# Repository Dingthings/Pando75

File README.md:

# Pando75
 Revised 75% keyboard based on Numpad65 project, inclusion of OLED and encoder module

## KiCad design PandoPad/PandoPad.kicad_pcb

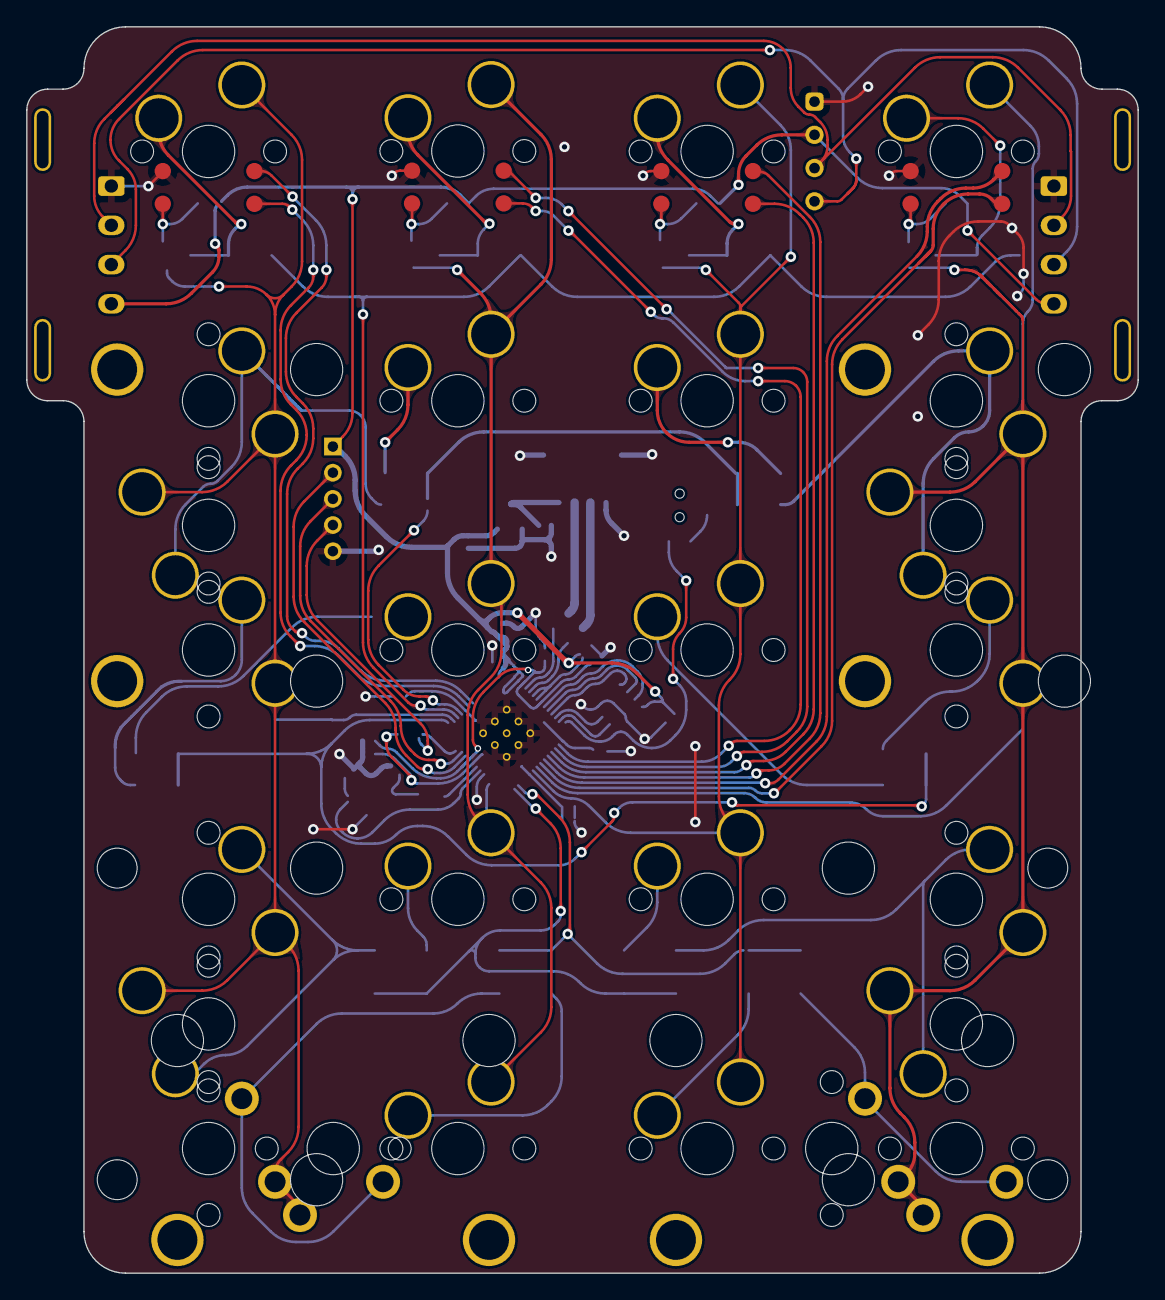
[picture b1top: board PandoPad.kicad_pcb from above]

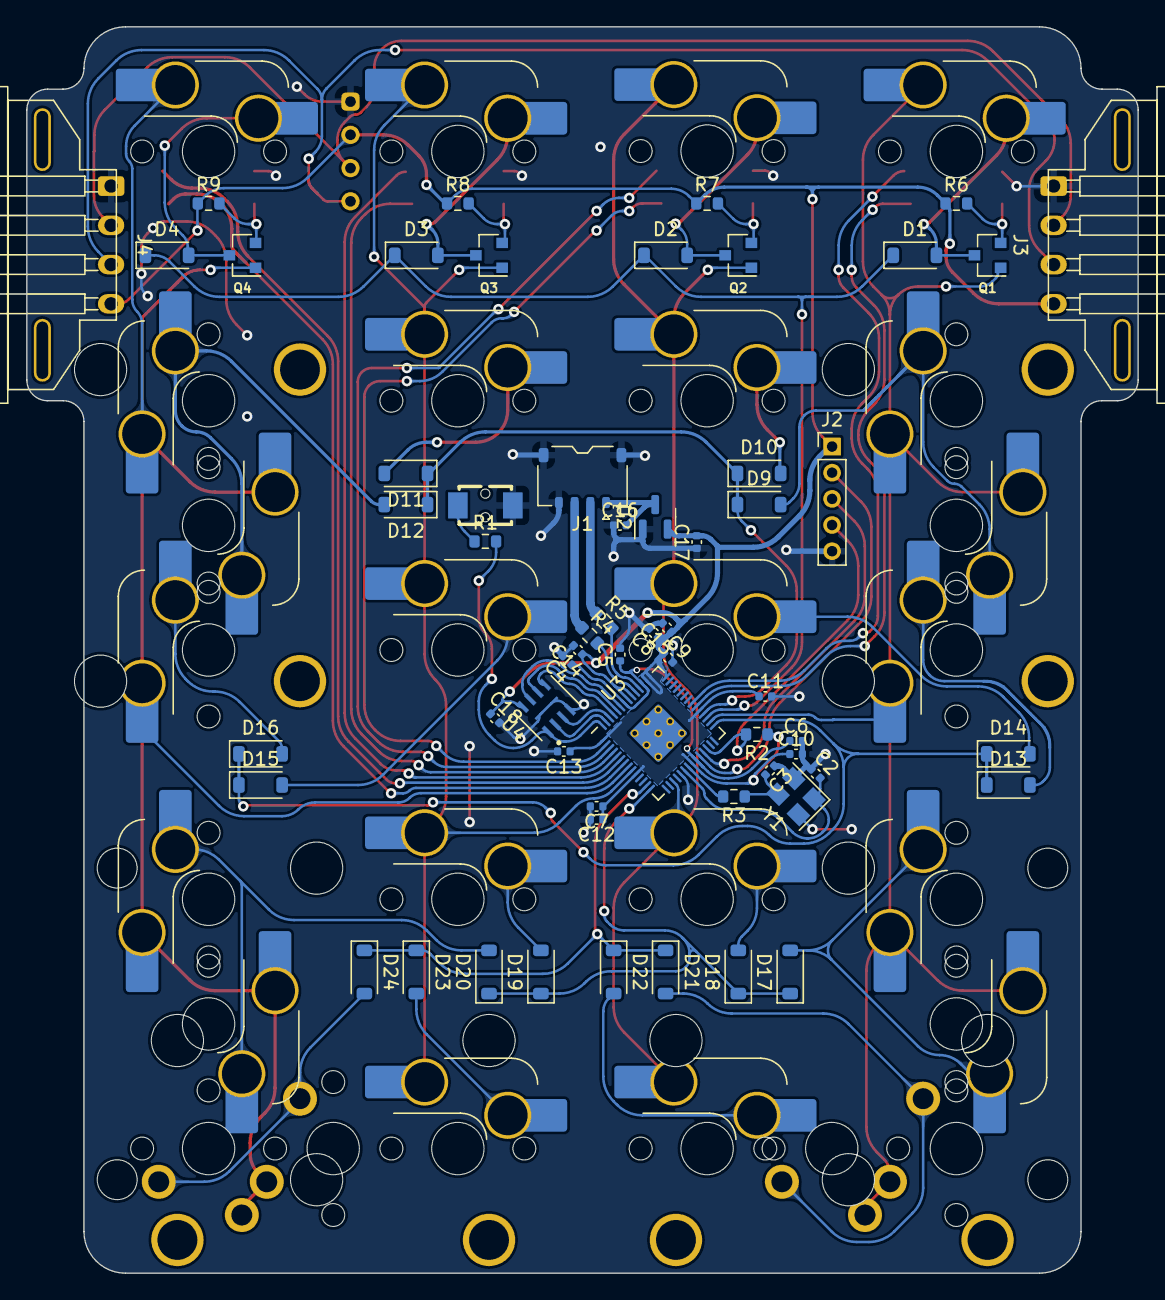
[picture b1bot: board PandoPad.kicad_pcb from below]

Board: 2 copper layers, 84.9 x 95.2 mm, 92 parts (57 on the bottom side), 64 nets.

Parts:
C2, C3: 22pF; C_0402_1005Metric
C4, C8, C16, C17: 1uF; C_0402_1005Metric
C5, C6, C9, C10, C11, C12, C13, C14, C15, C18: 100nF; C_0402_1005Metric
C7: 10uF; C_0402_1005Metric
D1, D2, D3, D4, D9, D10, D11, D12, D13, D14, D15, D16, D17, D18, D19, D20, D21, D22, D23, D24: 1N4148W; D_SOD-123
J1: 78171-0004; JST_ACH_BM04B-ACHSS-A-GAN-ETF_1x04-1MP_P1.20mm_Vertical
J2: Conn_01x05; PinHeader_1x05_P2.00mm_Vertical
J3: MalePogo; 1x04_3.00mm_Magnetic Pogo_Male
J4: FemalePogo; 1x04_3.00mm_Magnetic Pogo_Female
K1, K2, K3, K4: SW_Hotswap_Kailh_MX_plated_1.00u_Enc_Standalone
K9: 7; SW_Hotswap_Kailh_MX_plated_1.00u_Vias
K10: 8; SW_Hotswap_Kailh_MX_plated_1.00u_Vias
K11: 9; SW_Hotswap_Kailh_MX_plated_1.00u_Vias
K12: Right+; SW_Hotswap_Kailh_MX_plated_1.00u_Vias
K13: 4; SW_Hotswap_Kailh_MX_plated_1.00u_Vias
K14: 5; SW_Hotswap_Kailh_MX_plated_1.00u_Vias
K15: 6; SW_Hotswap_Kailh_MX_plated_1.00u_Vias
K16: OPT2; SW_Hotswap_Kailh_MX_plated_1.00u_Vias
K17: 1; SW_Hotswap_Kailh_MX_plated_1.00u_Vias
K18: 2; SW_Hotswap_Kailh_MX_plated_1.00u_Vias
K19: 3; SW_Hotswap_Kailh_MX_plated_1.00u_Vias
K20: REnt; SW_Hotswap_Kailh_MX_plated_1.00u_Vias
K22: LZero; SW_Hotswap_Millmax_1.00u
K23, K24: .; SW_Hotswap_Kailh_MX_plated_1.00u_Vias
K25: OPT5; SW_Hotswap_Millmax_1.00u
KO-1: Left+; SW_Hotswap_Kailh_MX_plated_1.00u_Vias
KO-2: OPT1; SW_Hotswap_Kailh_MX_plated_1.00u_Vias
KO-3: LEnt; SW_Hotswap_Kailh_MX_plated_1.00u_Vias
KO-4: OPT3; SW_Hotswap_Kailh_MX_plated_1.00u_Vias
KO-5: OPT4; SW_Hotswap_Millmax_1.00u
KO-6: OPT6; SW_Hotswap_Millmax_1.00u
P1: OLED2; OLED_v2
Q1, Q2, Q3, Q4: PMOS; SOT-23
R1, R3, R6, R7, R8, R9: 1k; R_0603_1608Metric
R2: R_Small; R_0603_1608Metric
R4, R5: 22R; R_0603_1608Metric
S1: PlusR; STAB_MX_P_2u
S2: EnterR; STAB_MX_2u
S3: PlusL; STAB_MX_P_2u
S4: EnterL; STAB_MX_2u
S5: ZeroR; STAB_MX_P_2u
S6: ZeroL; STAB_MX_P_2u
SW5: SW_Push; SW_C843666
U2: XC6206PxxxMR-Regulator_Linear; SOT-23
U3: RP2040; RP2040-QFN-56
U4: W25Q32JVUUIQ; SON80P400X300X60-10N
Y1: 12MHz; Crystal_SMD_3225-4Pin_3.2x2.5mm

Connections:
+1V1: C4.1, C5.1, C6.1, U3.23 (DVDD), U3.45 (VREG_VOUT), U3.50 (DVDD)
+3V3: C7.1, C8.1, C9.1, C10.1, C11.1, C12.1, C13.1, C14.1, C15.1, C17.2, C18.1, J2.1, J3.1, J4.1, P1.3, R2.1, R6.1, R7.1, R8.1, R9.1, U2.2 (VO), U3.1 (IOVDD), U3.10 (IOVDD), U3.22 (IOVDD), U3.33 (IOVDD), U3.42 (IOVDD), U3.43 (ADC_AVDD), U3.44 (VREG_VIN), U3.48 (USB_VDD), U3.49 (IOVDD), U4.8 (VCC)
+5V: C16.2, J1.1, U2.3 (VI)
/D_+: R4.2, U3.47 (D+)
/D_-: R5.2, U3.46 (D-)
/XTAL_O: C3.2, R3.1, Y1.3
/~USB_BOOT: R1.1, SW5.2
CS: R1.2, U3.56 (QSPI_SS_N), U4.1 (~CS)
D_N: J1.2, R5.1
D_P: J1.3, R4.1
E1A: K1.A, U3.34 (GPIO22)
E1B: K1.B, U3.35 (GPIO23)
E2A: K2.A, U3.2 (GPIO0)
E2B: K2.B, U3.3 (GPIO1)
E3A: K3.A, U3.4 (GPIO2)
E3B: K3.B, U3.5 (GPIO3)
E4A: K4.A, U3.7 (GPIO5)
E4B: K4.B, U3.6 (GPIO4)
GND: C2.1, C3.1, C4.2, C5.2, C6.2, C7.2, C8.2, C9.2, C10.2, C11.2, C12.2, C13.2, C14.2, C15.2, C16.1, C17.1, C18.2, J1.4, J1.MP (MountPin), J2.5, J3.4, J4.4, K1.C, K2.C, K3.C, K4.C, P1.4, SW5.1, U2.1 (GND), U3.19 (TESTEN), U3.57 (GND), U4.4 (GND), U4.9 (EXP), U4.10 (EXP), Y1.2, Y1.4
unnamed: D1.2 (A), K1.2, Q1.3 (S)
unnamed: D2.2 (A), K2.2, Q2.3 (S)
unnamed: D3.2 (A), K3.2, Q3.3 (S)
unnamed: D4.2 (A), K4.2, Q4.3 (S)
unnamed: D9.2 (A), K9.1, KO-1.1
unnamed: D10.2 (A), K10.1
unnamed: D11.2 (A), K11.1
unnamed: D12.2 (A), K12.1, KO-2.1
unnamed: D13.2 (A), K13.1
unnamed: D14.2 (A), K14.1
unnamed: D15.2 (A), K15.1
unnamed: D16.2 (A), K16.1
unnamed: D17.2 (A), K17.1, KO-3.1
unnamed: D18.2 (A), K18.1
unnamed: D19.2 (A), K19.1
unnamed: D20.2 (A), K20.1, KO-4.1
unnamed: D21.2 (A), K22.1, KO-5.1
unnamed: D22.2 (A), K23.1
unnamed: D23.2 (A), K24.1
unnamed: D24.2 (A), K25.1, KO-6.1
unnamed: K1.S, Q1.2 (G), R6.2
unnamed: K2.S, Q2.2 (G), R7.2
unnamed: K3.S, Q3.2 (G), R8.2
unnamed: K4.S, Q4.2 (G), R9.2
QSPI_CLK: U3.52 (QSPI_SCLK), U4.6 (SCK)
SCL: J3.3, J4.3, P1.2
SD0: U3.53 (QSPI_SD0), U4.5 (SI(I/O0))
SD1: U3.55 (QSPI_SD1), U4.2 (SO(I/O1))
SD2: U3.54 (QSPI_SD2), U4.3 (~WP~{(I/O2))
SD3: U3.51 (QSPI_SD3), U4.7 (~HOLD~{/~{RESET~{(I/O3))
SDA: J3.2, J4.2, P1.1
SWCLK: J2.2, U3.24 (SWCLK)
SWD: J2.3, U3.25 (SWDIO)
XTAL_IN: C2.2, U3.20 (XTAL_IN), Y1.1
XTAL_OUT: R3.2, U3.21 (XTAL_OUT)
col0: K1.1, K9.2, K13.2, K17.2, K22.2, KO-1.2, KO-3.2, KO-5.2, Q1.1 (D), U3.30 (GPIO19)
col1: K2.1, K10.2, K14.2, K18.2, K23.2, Q2.1 (D), U3.17 (GPIO14)
col2: K3.1, K11.2, K15.2, K19.2, K24.2, Q3.1 (D), U3.9 (GPIO7)
col3: K4.1, K12.2, K16.2, K20.2, K25.2, KO-2.2, KO-4.2, KO-6.2, Q4.1 (D), U3.8 (GPIO6)
row0: D1.1 (K), D2.1 (K), D3.1 (K), D4.1 (K), U3.31 (GPIO20)
row1: D9.1 (K), D10.1 (K), D11.1 (K), D12.1 (K), U3.32 (GPIO21)
row2: D13.1 (K), D14.1 (K), D15.1 (K), D16.1 (K), U3.29 (GPIO18)
row3: D17.1 (K), D18.1 (K), D19.1 (K), D20.1 (K), U3.14 (GPIO11)
row4: D21.1 (K), D22.1 (K), D23.1 (K), D24.1 (K), U3.13 (GPIO10)
~RESET: J2.4, R2.2, U3.26 (~RUN)

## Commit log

2023-03-13 Modified flash chip
2023-03-13 Added folders
2023-03-13 Removed 3d objects
2023-07-09 Finished Routing
